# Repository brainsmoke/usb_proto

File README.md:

# USB-C powered boards with programmable USB connectivity

This repository contains a few boards aimed at rapid prototyping.

The main idea is to save time by providing often-used components
and a microcontroller that can act as a USB-serial to UART
(usb-cdc-acm) device, a HID keyboard/keypad or run other simple
programs.

# Firmware (seems to work, no guarantees!)

* [usb_serial](firmware/usb_serial) USB serial to UART adapter firmware, with RTS/DTR signals & reset/boot signals for directly programming ESP32s.
* [usb_hid_keymatrix](firmware/usb_hid_keymatrix) USB HID Keypad firmware, for a keyboard matrix (max. 16 keys)
* [usb_hid_keymatrix](firmware/usb_hid_keymatrix_5x5) USB HID Keypad firmware, for a keyboard matrix (max. 25 keys)
* [usb_hid_simple](firmware/usb_hid_simple) USB HID Keypad firmware for a few buttons
* [flappy](firmware/flappy) Flappy bird controller / spacebar only USB HID Keypad
* [game_controller](firmware/game_controller) Gamepad controller / USB HID Keypad
* [popcalc](firmware/popcalc) USB device that 'pops calc'
* [led_segment_tester](firmware/led_segment_tester) tester firmware for a LED installation
* [obegraensad](firmware/obegraensad) USB-serial to 16 bit IKEA OBEGRÄNSAD display driver

# PCBs

## A protoboard with an STM32F042 for usb connectivity & GPIO / UART functionality.

Production files (JLCPCB): [gerbers](build/usb_proto/gerbers_jlc.zip) [BOM](build/usb_proto/bomfile_jlc.csv) [POS](build/usb_proto/posfile_jlc.csv)

Cases: [basic](build/usb_proto/case.stl) [hexagon](build/usb_proto/case_almost_regular_hexagon.stl) [keyswitches](build/usb_proto/case_keyswitches_8.stl) [led strips](build/usb_proto/case_led_strip_connector.stl)

* 5v USB-C fed (with 5k1 resistors for true USB-C compatibility)
* 3v3 linear regulator
* STM32F042G6 microcontroller (with xtal-less 12mbit USB support)
* A button to boot the STM32 in DFU mode
* GPIO Port A pins 0 to 7 broken out
* GPIO Port B pins 6 & 7 broken out (for UART TX/RX)
* 4 general purpose LEDs
* 3 general purpose buttons
* A 21 column breadboard-style protoboard
* size: 47x77mm
* 4 M3 holes 40mm and 70mm apart

## An STM32F042 breakout board

Production files (JLCPCB): [gerbers](build/usb_mini_io/gerbers_jlc.zip) [BOM](build/usb_mini_io/bomfile_jlc.csv) [POS](build/usb_mini_io/posfile_jlc.csv)

Cases: [keypad (keycaps flush)](build/usb_mini_io/keypad.stl) [keypad (keyswitches visible)](build/usb_mini_io/old_keypad.stl) [single key controller](build/usb_mini_io/single_key.stl)

* for smaller enclosures (27x22mm)
* I/O & firmware compatible with the protoboard
* 5v USB-C fed (with 5k1 resistors for true USB-C compatibility)
* 3v3 linear regulator
* STM32F042G6 microcontroller (with xtal-less 12mbit USB support)
* A button to boot the STM32 in DFU mode
* no LEDs / general purpose buttons / protoboard space
* 2 M3 holes 20mm apart

# USB <-> USB 'null-modem' (but electrically isolated) [UNTESTED]

# JTAG/SWD programmer with USB-C connector
 
Production files (JLCPCB): [gerbers](build/swd_prog/gerbers_jlc.zip) [BOM](build/swd_prog/bomfile_jlc.csv) [POS](build/swd_prog/posfile_jlc.csv)
 
Cases: [basic](build/swd_prog/case.stl) [all headers](build/swd_prog/case_add.stl)

# Padauk programmer with USB-C connector

Production files (JLCPCB): [gerbers](build/pdk_prog/gerbers_jlc.zip) [BOM](build/pdk_prog/bomfile_jlc.csv) [POS](build/pdk_prog/posfile_jlc.csv)
 
Case: [case](build/pdk_prog/case.stl)

## (old) USB-C Fed Protoboard

The first version of the protoboard did not have a microcontroller:
[pcb/simple](pcb/simple)

# License

* The hardware (schematic / PCB / production files / case models ) is Licensed CC-BY-4.0
* The firmware (in the firmware directory) uses libopencm3 which is licensed LGPLv3 and
  all code specific to this project is distributed under the MIT license.
* This repo contains nothing vibe-coded
* LLM assisted contributions not welcome

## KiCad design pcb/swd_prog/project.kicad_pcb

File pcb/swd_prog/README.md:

# JTAG/SWD programmer with USB-C connector

Production files (JLCPCB): [gerbers](../../build/swd_prog/gerbers_jlc.zip) [BOM](../../build/swd_prog/bomfile_jlc.csv) [POS](../../build/swd_prog/posfile_jlc.csv)

Cases: [basic](../../build/swd_prog/case.stl), [all headers](../../build/swd_prog/case_all.stl)

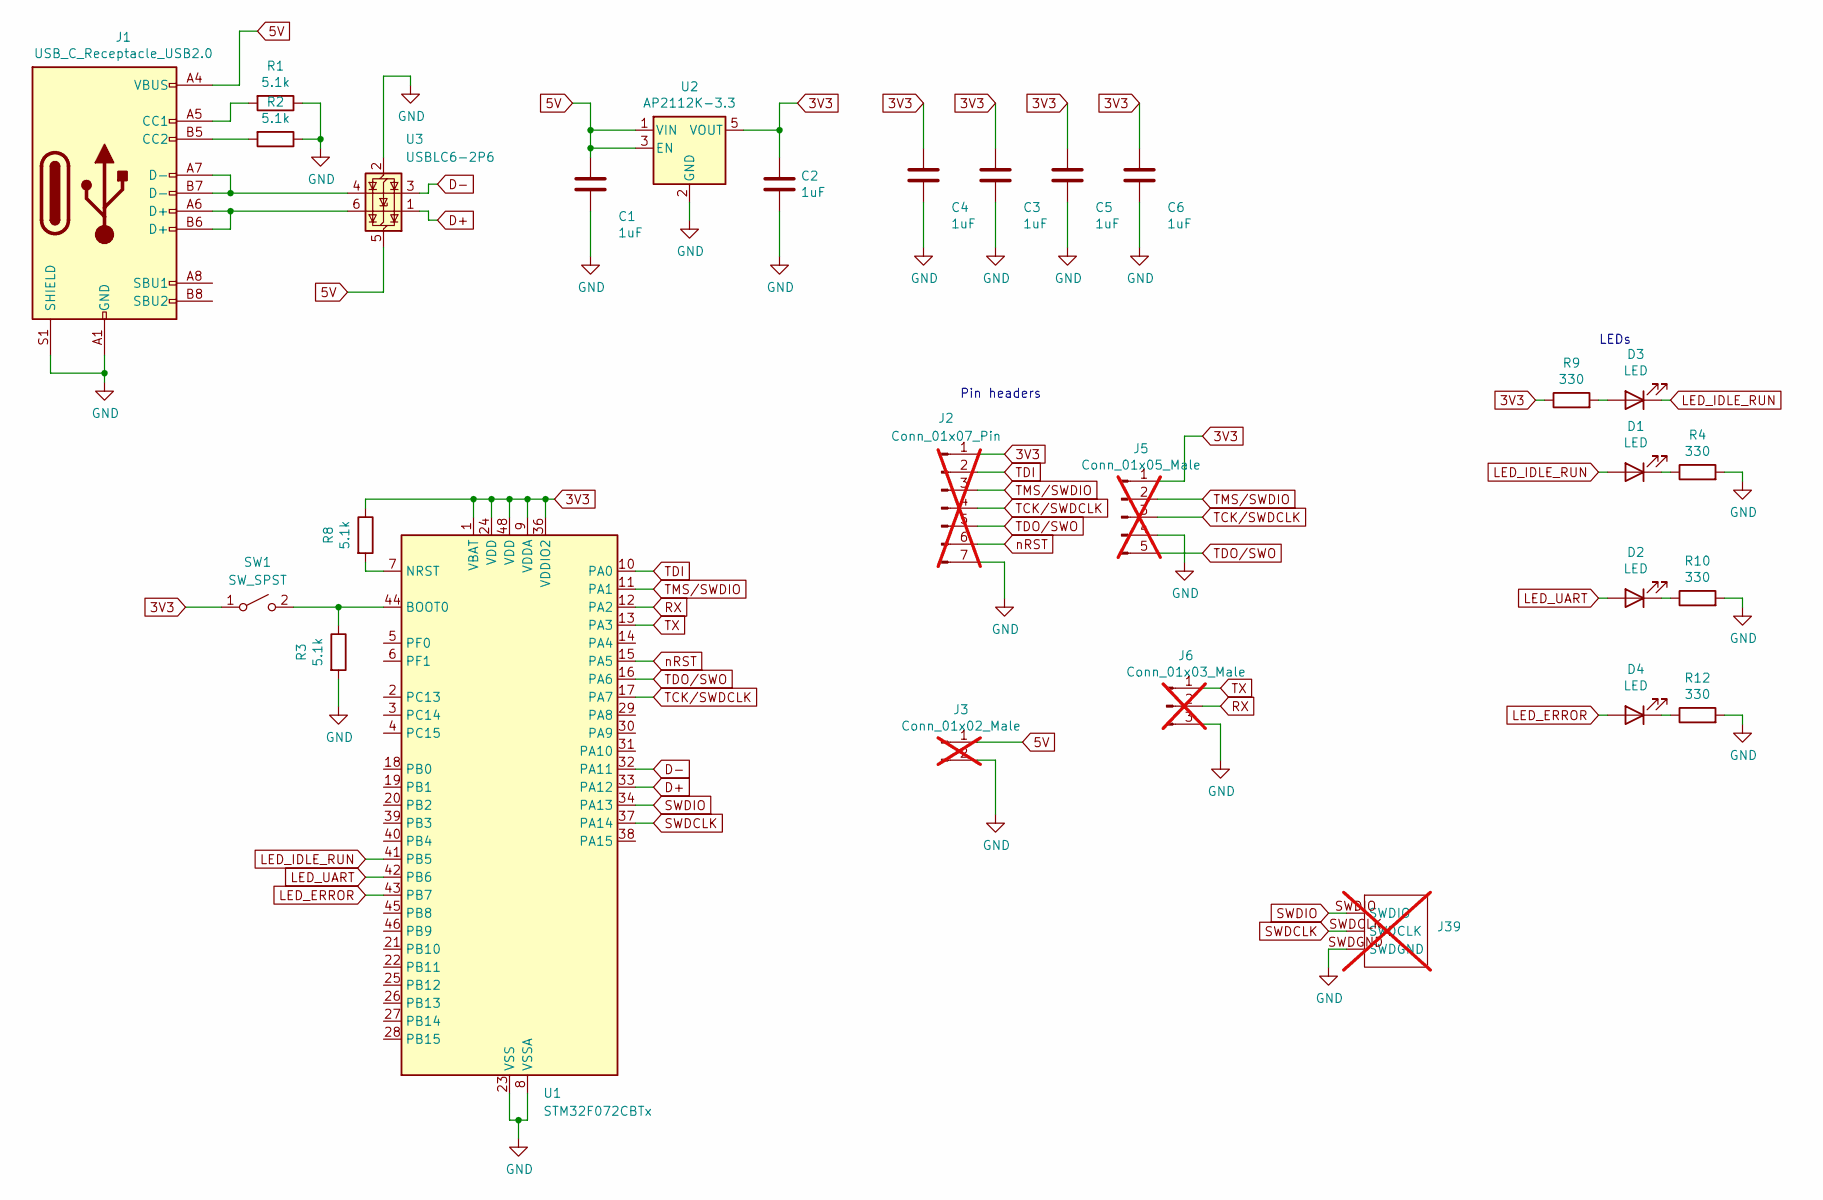
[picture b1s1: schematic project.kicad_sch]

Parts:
C1, C2, C3, C4, C5, C6: 1uF; C_0402_1005Metric; LCSC C52923
D1: LED; LED_0603_1608Metric; LCSC C72038
D2, D3: LED; LED_0603_1608Metric; LCSC C12065
D4: LED; LED_0603_1608Metric; LCSC C2286
J1: USB_C_Receptacle_USB2.0; USB_C_Receptacle_HRO_TYPE-C-31-M-12; LCSC C165948
J2: Conn_01x07_Pin; PinHeader_1x07_P2.54mm_Vertical; not fitted
J3: Conn_01x02_Male; PinHeader_1x02_P2.54mm_Vertical; not fitted
J5: Conn_01x05_Male; PinHeader_1x05_P2.54mm_Vertical; not fitted
J6: Conn_01x03_Male; PinHeader_1x03_P2.54mm_Vertical; not fitted
J39: SWDHeader_covered; not fitted
R1, R2, R3, R8: 5.1k; R_0402_1005Metric; LCSC C25905
R4, R9, R10, R12: 330; R_0402_1005Metric; LCSC C25104
SW1: SW_SPST; SW_Push_1P1T_NO_CK_KMR2; LCSC C318893
U1: STM32F072CBTx; LQFP-48_7x7mm_P0.5mm; LCSC C81720
U2: AP2112K-3.3; SOT-23-5; LCSC C51118
U3: USBLC6-2P6; SOT-666; LCSC C15999

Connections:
3V3: C2.1, C3.1, C4.1, C5.1, C6.1, J2.1, J5.1, R8.1, R9.1, SW1.1 (A), U1.1 (VBAT), U1.9 (VDDA), U1.24 (VDD), U1.36 (VDDIO2), U1.48 (VDD), U2.5 (VOUT)
5V: C1.1, J1.A4 (VBUS), J1.A9 (VBUS), J1.B4 (VBUS), J1.B9 (VBUS), J3.1, U2.1 (VIN), U2.3 (EN), U3.5 (VBUS)
D+: U1.33 (PA12), U3.1 (I/O1)
D-: U1.32 (PA11), U3.3 (I/O2)
GND: C1.2, C2.2, C3.2, C4.2, C5.2, C6.2, J1.A1 (GND), J1.A12 (GND), J1.B1 (GND), J1.B12 (GND), J1.S1 (SHIELD), J2.7, J3.2, J5.4, J6.3, J39.SWDGND, R1.1, R2.1, R3.2, R4.2, R10.2, R12.2, U1.8 (VSSA), U1.23 (VSS), U1.35 (VSS), U1.47 (VSS), U2.2 (GND), U3.2 (GND)
LED_ERROR: D4.2 (A), U1.43 (PB7)
LED_IDLE_RUN: D1.2 (A), D3.1 (K), U1.41 (PB5)
LED_UART: D2.2 (A), U1.42 (PB6)
unnamed: D1.1 (K), R4.1
unnamed: D2.1 (K), R10.1
unnamed: D3.2 (A), R9.2
unnamed: D4.1 (K), R12.1
unnamed: J1.A5 (CC1), R1.2
unnamed: J1.B5 (CC2), R2.2
unnamed: J1.A6 (D+), J1.B6 (D+), U3.6 (I/O1)
unnamed: J1.A7 (D-), J1.B7 (D-), U3.4 (I/O2)
unnamed: R3.1, SW1.2 (B), U1.44 (BOOT0)
unnamed: R8.2, U1.7 (NRST)
RX: J6.2, U1.12 (PA2)
SWDCLK: J39.SWDCLK, U1.37 (PA14)
SWDIO: J39.SWDIO, U1.34 (PA13)
TCK/SWDCLK: J2.4, J5.3, U1.17 (PA7)
TDI: J2.2, U1.10 (PA0)
TDO/SWO: J2.5, J5.5, U1.16 (PA6)
TMS/SWDIO: J2.3, J5.2, U1.11 (PA1)
TX: J6.1, U1.13 (PA3)
nRST: J2.6, U1.15 (PA5)

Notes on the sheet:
Pin headers
LEDs

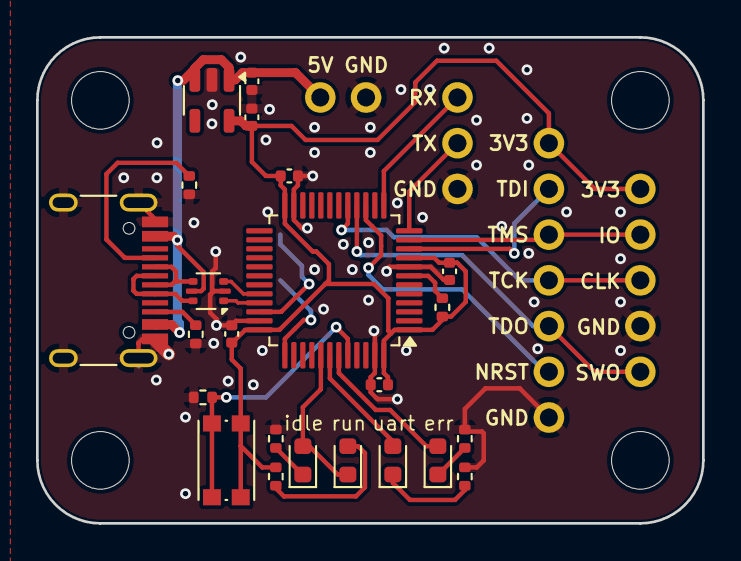
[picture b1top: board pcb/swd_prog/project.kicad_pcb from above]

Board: 2 copper layers, 37.0 x 27.0 mm, 28 parts (1 on the bottom side), 27 nets.

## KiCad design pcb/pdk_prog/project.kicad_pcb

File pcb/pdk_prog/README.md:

# Padauk programmer with USB-C connector

Production files (JLCPCB): [gerbers](../../build/pdk_prog/gerbers_jlc.zip) [BOM](../../build/pdk_prog/bomfile_jlc.csv) [POS](../../build/pdk_prog/posfile_jlc.csv)

Case: [case](../../build/pdk_prog/case.stl)

Circuit adapted from:

  https://github.com/free-pdk/easy-pdk-programmer-lite-hardware

Which in turn was adapted from:

  https://github.com/free-pdk/easy-pdk-programmer-hardware

Runs:

  https://github.com/free-pdk/easy-pdk-programmer-software

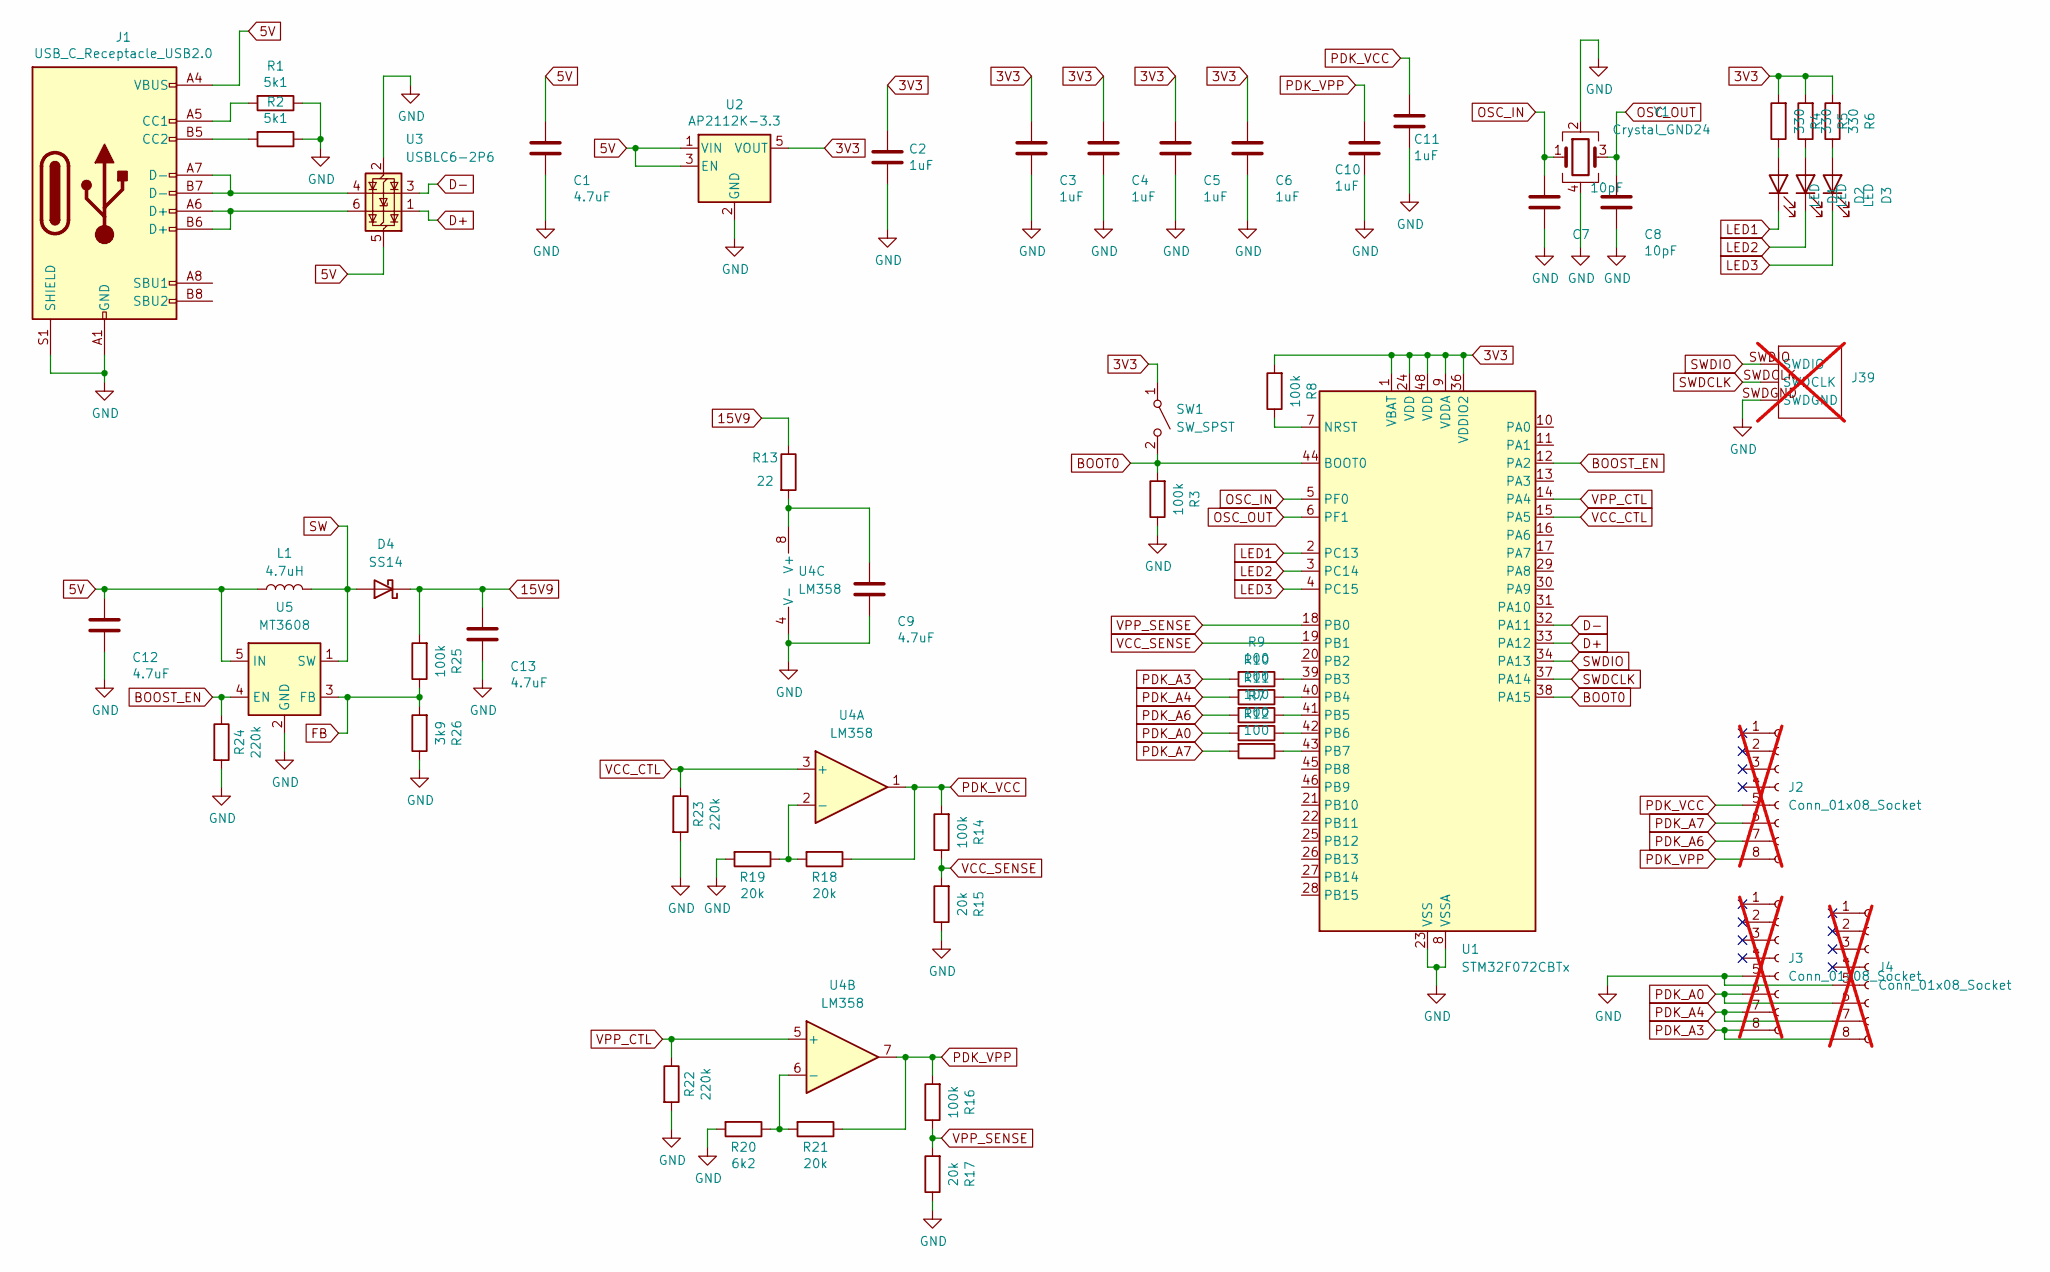
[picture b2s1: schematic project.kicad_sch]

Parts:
C1, C9, C12, C13: 4.7uF; C_0603_1608Metric; LCSC C19666
C2, C3, C4, C5, C6, C10, C11: 1uF; C_0402_1005Metric; LCSC C52923
C7, C8: 10pF; C_0402_1005Metric; LCSC C32949
D1, D2, D3: LED; LED_0603_1608Metric; LCSC C2286
D4: SS14; D_SMA; LCSC C2480
J1: USB_C_Receptacle_USB2.0; USB_C_Receptacle_HRO_TYPE-C-31-M-12; LCSC C165948
J2, J3, J4: Conn_01x08_Socket; PinSocket_1x08_P2.54mm_Vertical; not fitted
J39: SWDHeader_covered; not fitted
L1: 4.7uH; L_Wuerth_MAPI-3015; LCSC C7427089
R1, R2: 5k1; R_0402_1005Metric; LCSC C25905
R3, R8, R14, R16, R25: 100k; R_0402_1005Metric; LCSC C25741
R4, R5, R6: 330; R_0402_1005Metric; LCSC C25104
R7, R9, R10, R11, R12: 100; R_0402_1005Metric; LCSC C25076
R13: 22; R_0402_1005Metric; LCSC C25092
R15, R17, R18, R19, R21: 20k; R_0402_1005Metric; LCSC C25765
R20: 6k2; R_0603_1608Metric; LCSC C4260
R22, R23, R24: 220k; R_0402_1005Metric; LCSC C25767
R26: 3k9; R_0402_1005Metric; LCSC C51721
SW1: SW_SPST; SW_Push_1P1T_NO_CK_KMR2; LCSC C318893
U1: STM32F072CBTx; LQFP-48_7x7mm_P0.5mm; LCSC C81720
U2: AP2112K-3.3; SOT-23-5; LCSC C51118
U3: USBLC6-2P6; SOT-666; LCSC C15999
U4: LM358; SOIC-8_3.9x4.9mm_P1.27mm; LCSC C7950
U5: MT3608; SOT-23-6; LCSC C84817
Y1: Crystal_GND24; Crystal_SMD_3225-4Pin_3.2x2.5mm; LCSC C400090

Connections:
3V3: C2.1, C3.1, C4.1, C5.1, C6.1, R4.2, R5.2, R6.2, R8.2, SW1.1 (A), U1.1 (VBAT), U1.9 (VDDA), U1.24 (VDD), U1.36 (VDDIO2), U1.48 (VDD), U2.5 (VOUT)
5V: C1.1, C12.1, J1.A4 (VBUS), J1.A9 (VBUS), J1.B4 (VBUS), J1.B9 (VBUS), L1.1, U2.1 (VIN), U2.3 (EN), U3.5 (VBUS), U5.5 (IN)
15V9: C13.1, D4.1 (K), R13.1, R25.2
BOOST_EN: R24.1, U1.12 (PA2), U5.4 (EN)
BOOT0: R3.2, SW1.2 (B), U1.38 (PA15), U1.44 (BOOT0)
D+: U1.33 (PA12), U3.1 (I/O1)
D-: U1.32 (PA11), U3.3 (I/O2)
FB: R25.1, R26.2, U5.3 (FB)
GND: C1.2, C2.2, C3.2, C4.2, C5.2, C6.2, C7.2, C8.2, C9.2, C10.2, C11.2, C12.2, C13.2, J1.A1 (GND), J1.A12 (GND), J1.B1 (GND), J1.B12 (GND), J1.S1 (SHIELD), J3.5, J4.5, J39.SWDGND, R1.1, R2.1, R3.1, R15.1, R17.1, R19.2, R20.2, R22.2, R23.2, R24.2, R26.1, U1.8 (VSSA), U1.23 (VSS), U1.35 (VSS), U1.47 (VSS), U2.2 (GND), U3.2 (GND), U4.4 (V-), U5.2 (GND), Y1.2, Y1.4
LED1: D1.1 (K), U1.2 (PC13)
LED2: D2.1 (K), U1.3 (PC14)
LED3: D3.1 (K), U1.4 (PC15)
unnamed: D1.2 (A), R4.1
unnamed: D2.2 (A), R5.1
unnamed: D3.2 (A), R6.1
unnamed: J1.A5 (CC1), R1.2
unnamed: J1.B5 (CC2), R2.2
unnamed: J1.A6 (D+), J1.B6 (D+), U3.6 (I/O1)
unnamed: J1.A7 (D-), J1.B7 (D-), U3.4 (I/O2)
unnamed: R8.1, U1.7 (NRST)
unnamed: R9.1, U1.39 (PB3)
unnamed: R10.1, U1.40 (PB4)
unnamed: R11.1, U1.41 (PB5)
unnamed: R7.1, U1.42 (PB6)
unnamed: R12.1, U1.43 (PB7)
unnamed: R18.2, R19.1, U4.2 (-)
unnamed: R20.1, R21.2, U4.6 (-)
unnamed: C9.1, R13.2, U4.8 (V+)
OSC_IN: C7.1, U1.5 (PF0), Y1.1
OSC_OUT: C8.1, U1.6 (PF1), Y1.3
PDK_A0: J3.6, J4.6, R7.2
PDK_A3: J3.8, J4.8, R9.2
PDK_A4: J3.7, J4.7, R10.2
PDK_A6: J2.7, R11.2
PDK_A7: J2.6, R12.2
PDK_VCC: C11.1, J2.5, R14.2, R18.1, U4.1
PDK_VPP: C10.1, J2.8, R16.2, R21.1, U4.7
SW: D4.2 (A), L1.2, U5.1 (SW)
SWDCLK: J39.SWDCLK, U1.37 (PA14)
SWDIO: J39.SWDIO, U1.34 (PA13)
VCC_CTL: R23.1, U1.15 (PA5), U4.3 (+)
VCC_SENSE: R14.1, R15.2, U1.19 (PB1)
VPP_CTL: R22.1, U1.14 (PA4), U4.5 (+)
VPP_SENSE: R16.1, R17.2, U1.18 (PB0)

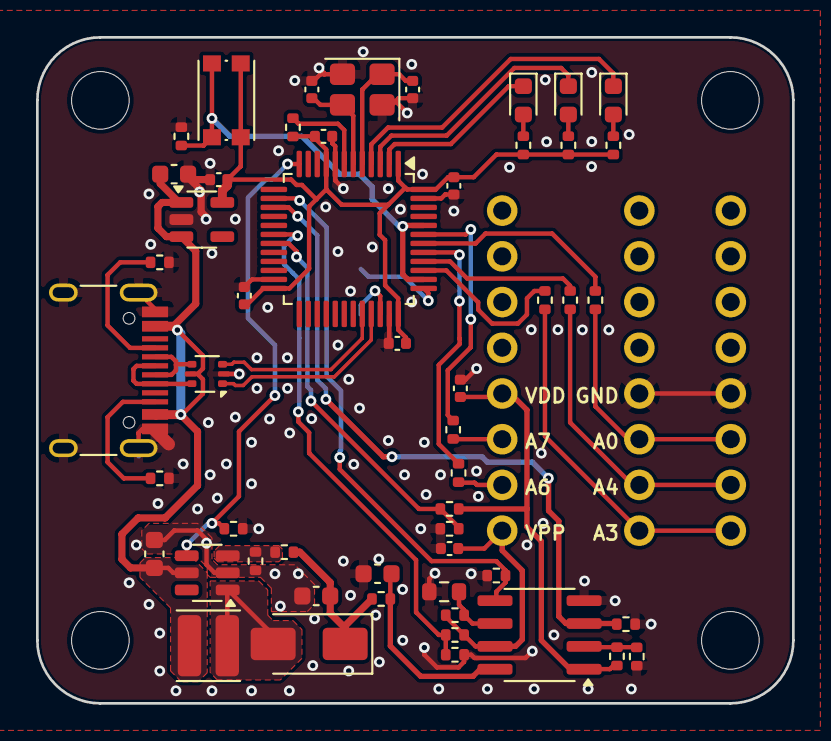
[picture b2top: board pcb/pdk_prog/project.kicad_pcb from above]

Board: 2 copper layers, 42.0 x 37.0 mm, 56 parts (1 on the bottom side), 44 nets.

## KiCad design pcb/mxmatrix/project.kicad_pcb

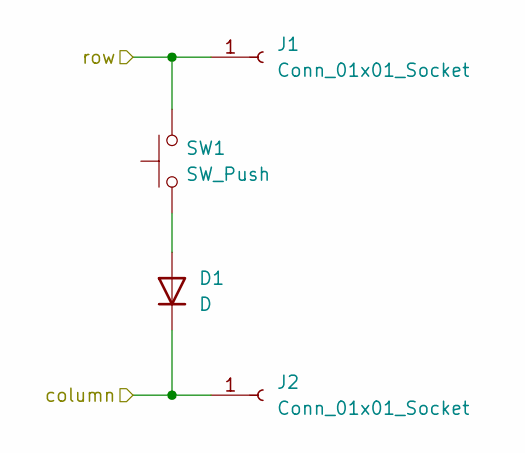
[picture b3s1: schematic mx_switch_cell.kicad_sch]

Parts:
D1: D; D_SOD-123
J1, J2: Conn_01x01_Socket; PinSocket_1x01_P2.54mm_Vertical
SW1: SW_Push; SW_Cherry_MX_1.00u_PCB

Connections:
/mx_switch_cell/column: D1.1 (K), J2.1; also elsewhere on the board
/mx_switch_cell/row: J1.1, SW1.2; also elsewhere on the board
unnamed: D1.2 (A), SW1.1

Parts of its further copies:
D2, D3, D4, D5, D6, D7, D8, D9, D10, D11, D12, D13, D14, D15, D16, D17, D18, D19, D20, D21, D22, D23, D24, D25: D; D_SOD-123
J3, J4, J5, J6, J7, J8, J9, J10, J11, J12, J13, J14, J15, J16, J17, J18, J19, J20, J21, J22, J23, J24, J25, J26, J27, J28, J29, J30, J31, J32, J33, J34, J35, J36, J37, J38, J39, J40, J41, J42, J43, J44, J45, J46, J47, J48, J49, J50: Conn_01x01_Socket; PinSocket_1x01_P2.54mm_Vertical
SW2, SW3, SW4, SW5, SW6, SW7, SW8, SW9, SW10, SW11, SW12, SW13, SW14, SW15, SW16, SW17, SW18, SW19, SW20, SW21, SW22, SW23, SW24, SW25: SW_Push; SW_Cherry_MX_1.00u_PCB

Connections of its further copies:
/mx_switch_cell1/row: J3.1, J13.1, J23.1, J33.1, J43.1, SW2.2, SW7.2, SW12.2, SW17.2, SW22.2
/mx_switch_cell5/column: D6.1 (K), D7.1 (K), D8.1 (K), D9.1 (K), D10.1 (K), J12.1, J14.1, J16.1, J18.1, J20.1
/mx_switch_cell10/column: D11.1 (K), D12.1 (K), D13.1 (K), D14.1 (K), D15.1 (K), J22.1, J24.1, J26.1, J28.1, J30.1
/mx_switch_cell12/row: J5.1, J15.1, J25.1, J35.1, J45.1, SW3.2, SW8.2, SW13.2, SW18.2, SW23.2
/mx_switch_cell13/row: J7.1, J17.1, J27.1, J37.1, J47.1, SW4.2, SW9.2, SW14.2, SW19.2, SW24.2
/mx_switch_cell14/row: J9.1, J19.1, J29.1, J39.1, J49.1, SW5.2, SW10.2, SW15.2, SW20.2, SW25.2
/mx_switch_cell15/column: D16.1 (K), D17.1 (K), D18.1 (K), D19.1 (K), D20.1 (K), J32.1, J34.1, J36.1, J38.1, J40.1
/mx_switch_cell20/column: D21.1 (K), D22.1 (K), D23.1 (K), D24.1 (K), D25.1 (K), J42.1, J44.1, J46.1, J48.1, J50.1
/mx_switch_cell/column: D2.1 (K), D3.1 (K), D4.1 (K), D5.1 (K), J4.1, J6.1, J8.1, J10.1; also elsewhere on the board
/mx_switch_cell/row: J11.1, J21.1, J31.1, J41.1, SW6.2, SW11.2, SW16.2, SW21.2; also elsewhere on the board
unnamed: D2.2 (A), SW2.1
unnamed: D3.2 (A), SW3.1
unnamed: D4.2 (A), SW4.1
unnamed: D5.2 (A), SW5.1
unnamed: D6.2 (A), SW6.1
unnamed: D7.2 (A), SW7.1
unnamed: D8.2 (A), SW8.1
unnamed: D9.2 (A), SW9.1
unnamed: D10.2 (A), SW10.1
unnamed: D11.2 (A), SW11.1
unnamed: D12.2 (A), SW12.1
unnamed: D13.2 (A), SW13.1
unnamed: D14.2 (A), SW14.1
unnamed: D15.2 (A), SW15.1
unnamed: D16.2 (A), SW16.1
unnamed: D17.2 (A), SW17.1
unnamed: D18.2 (A), SW18.1
unnamed: D19.2 (A), SW19.1
unnamed: D20.2 (A), SW20.1
unnamed: D21.2 (A), SW21.1
unnamed: D22.2 (A), SW22.1
unnamed: D23.2 (A), SW23.1
unnamed: D24.2 (A), SW24.1
unnamed: D25.2 (A), SW25.1

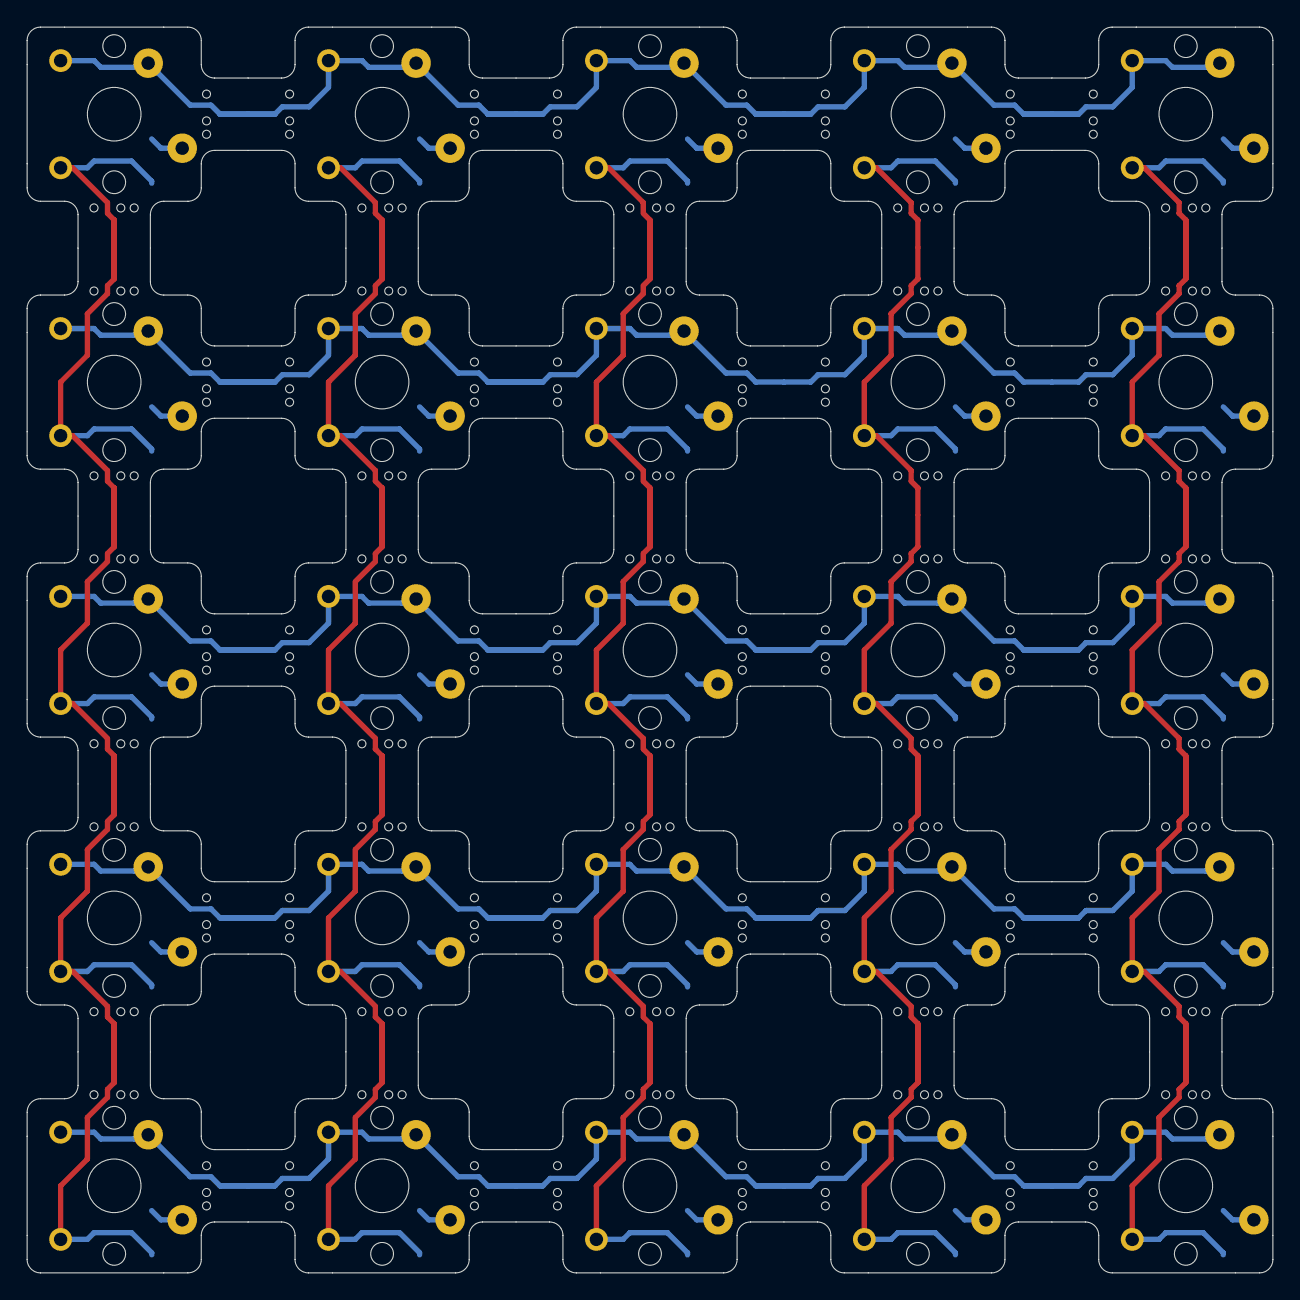
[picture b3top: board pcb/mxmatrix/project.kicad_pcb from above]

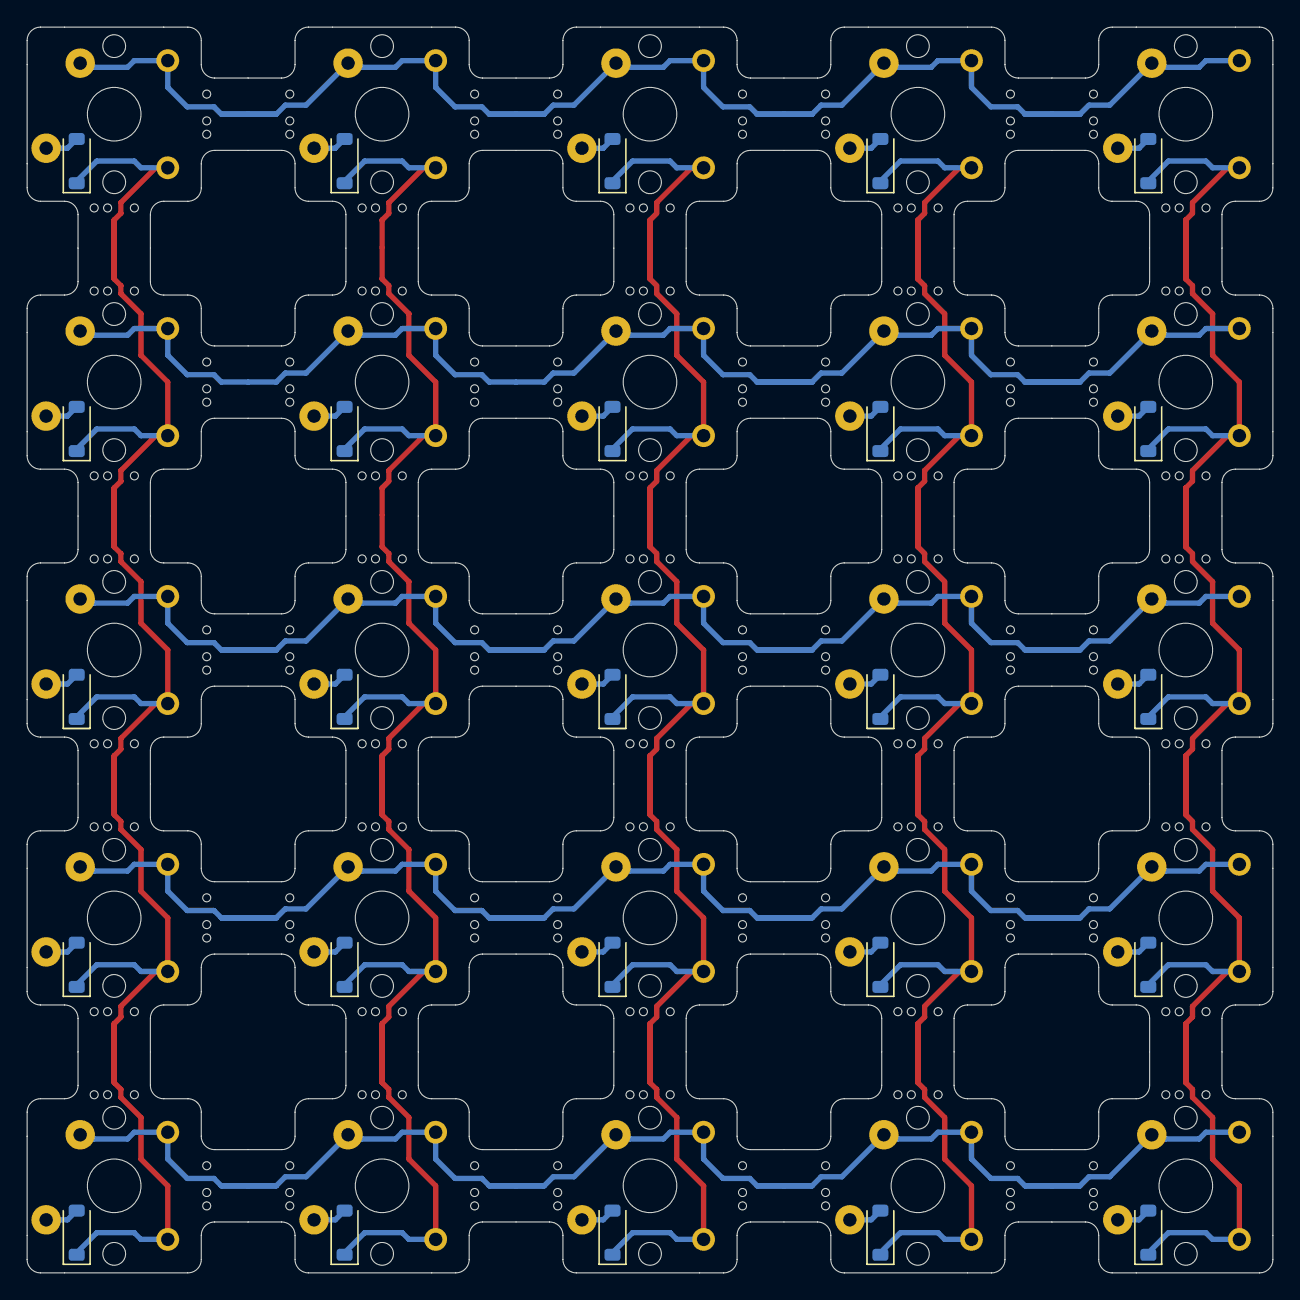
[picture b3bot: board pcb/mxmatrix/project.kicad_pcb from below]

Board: 2 copper layers, 93.0 x 93.0 mm, 100 parts (75 on the bottom side), 35 nets.

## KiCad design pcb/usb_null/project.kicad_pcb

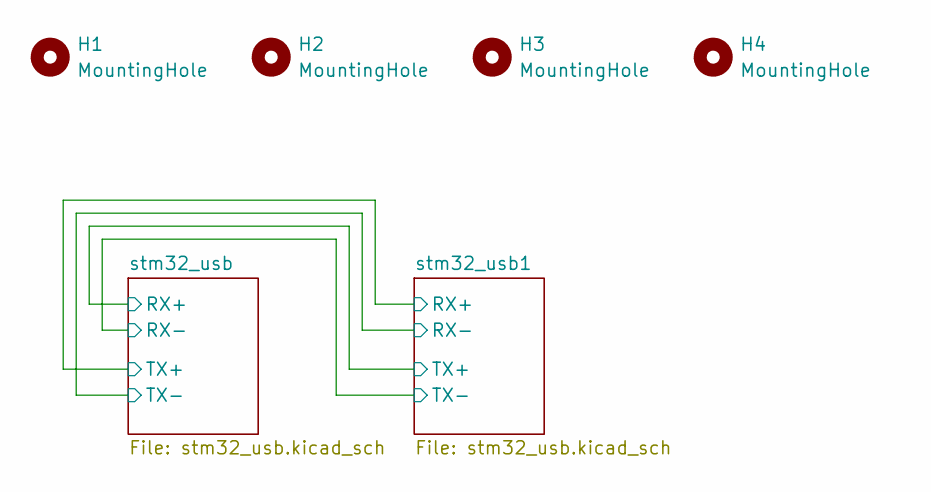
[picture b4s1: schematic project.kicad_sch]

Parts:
H1, H2, H3, H4: MountingHole; MountingHole_3.2mm_M3_DIN965

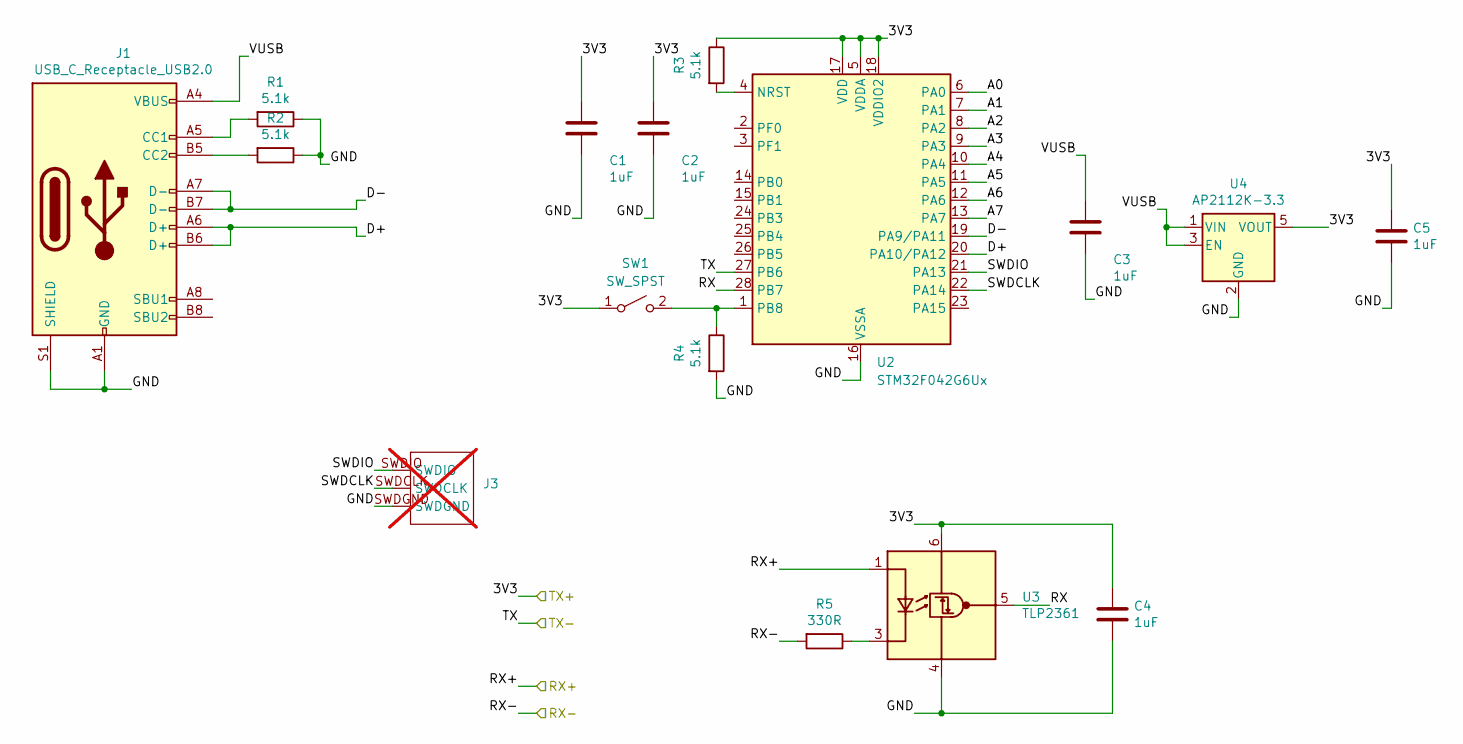
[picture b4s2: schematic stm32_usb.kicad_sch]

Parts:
C1, C2, C3, C4, C5: 1uF; C_0402_1005Metric; LCSC C52923
J1: USB_C_Receptacle_USB2.0; USB_C_Receptacle_HRO_TYPE-C-31-M-12; LCSC C165948
J3: SWDHeader; not fitted
R1, R2, R3, R4: 5.1k; R_0402_1005Metric; LCSC C25905
R5: 330R; R_0402_1005Metric; LCSC C25104
SW1: SW_SPST; SW_Push_1P1T_NO_CK_KMR2; LCSC C318893
U2: STM32F042G6Ux; QFN-28_4x4mm_P0.5mm; LCSC C961597
U3: TLP2361; SO-5_4.4x3.6mm_P1.27mm; LCSC C107626
U4: AP2112K-3.3; SOT-23-5; LCSC C51118

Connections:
/stm32_usb/3V3: C1.1, C2.1, C4.1, C5.1, R3.1, SW1.1 (A), U2.5 (VDDA), U2.17 (VDD), U2.18 (VDDIO2), U3.6 (VDD), U4.5 (VOUT); also elsewhere on the board
/stm32_usb/A0: U2.6 (PA0)
/stm32_usb/A1: U2.7 (PA1)
/stm32_usb/A2: U2.8 (PA2)
/stm32_usb/A3: U2.9 (PA3)
/stm32_usb/A4: U2.10 (PA4)
/stm32_usb/A5: U2.11 (PA5)
/stm32_usb/A6: U2.12 (PA6)
/stm32_usb/A7: U2.13 (PA7)
/stm32_usb/D+: J1.A6 (D+), J1.B6 (D+), U2.20 (PA10/PA12)
/stm32_usb/D-: J1.A7 (D-), J1.B7 (D-), U2.19 (PA9/PA11)
/stm32_usb/GND: C1.2, C2.2, C3.2, C4.2, C5.2, J1.A1 (GND), J1.A12 (GND), J1.B1 (GND), J1.B12 (GND), J1.S1 (SHIELD), J3.SWDGND, R1.1, R2.1, R4.2, U2.16 (VSSA), U3.4 (GND), U4.2 (GND)
/stm32_usb/RX: U2.28 (PB7), U3.5 (VO)
/stm32_usb/RX+: U3.1 (A); also elsewhere on the board
/stm32_usb/RX-: R5.2; also elsewhere on the board
/stm32_usb/SWDCLK: J3.SWDCLK, U2.22 (PA14)
/stm32_usb/SWDIO: J3.SWDIO, U2.21 (PA13)
/stm32_usb/TX: U2.27 (PB6); also elsewhere on the board
/stm32_usb/VUSB: C3.1, J1.A4 (VBUS), J1.A9 (VBUS), J1.B4 (VBUS), J1.B9 (VBUS), U4.1 (VIN), U4.3 (EN)
unnamed: J1.A5 (CC1), R1.2
unnamed: J1.B5 (CC2), R2.2
unnamed: R4.1, SW1.2 (B), U2.1 (PB8)
unnamed: R3.2, U2.4 (NRST)
unnamed: R5.1, U3.3 (K)

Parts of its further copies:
C6, C7, C8, C9, C10: 1uF; C_0402_1005Metric; LCSC C52923
J4: USB_C_Receptacle_USB2.0; USB_C_Receptacle_HRO_TYPE-C-31-M-12; LCSC C165948
J6: SWDHeader; not fitted
R6, R7, R8, R9: 5.1k; R_0402_1005Metric; LCSC C25905
R10: 330R; R_0402_1005Metric; LCSC C25104
SW2: SW_SPST; SW_Push_1P1T_NO_CK_KMR2; LCSC C318893
U6: STM32F042G6Ux; QFN-28_4x4mm_P0.5mm; LCSC C961597
U7: TLP2361; SO-5_4.4x3.6mm_P1.27mm; LCSC C107626
U8: AP2112K-3.3; SOT-23-5; LCSC C51118

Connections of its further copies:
/stm32_usb1/A0: U6.6 (PA0)
/stm32_usb1/A1: U6.7 (PA1)
/stm32_usb1/A2: U6.8 (PA2)
/stm32_usb1/A3: U6.9 (PA3)
/stm32_usb1/A4: U6.10 (PA4)
/stm32_usb1/A5: U6.11 (PA5)
/stm32_usb1/A6: U6.12 (PA6)
/stm32_usb1/A7: U6.13 (PA7)
/stm32_usb1/D+: J4.A6 (D+), J4.B6 (D+), U6.20 (PA10/PA12)
/stm32_usb1/D-: J4.A7 (D-), J4.B7 (D-), U6.19 (PA9/PA11)
/stm32_usb1/GND: C6.2, C7.2, C8.2, C9.2, C10.2, J4.A1 (GND), J4.A12 (GND), J4.B1 (GND), J4.B12 (GND), J4.S1 (SHIELD), J6.SWDGND, R6.1, R7.1, R9.2, U6.16 (VSSA), U7.4 (GND), U8.2 (GND)
/stm32_usb1/RX: U6.28 (PB7), U7.5 (VO)
/stm32_usb1/SWDCLK: J6.SWDCLK, U6.22 (PA14)
/stm32_usb1/SWDIO: J6.SWDIO, U6.21 (PA13)
/stm32_usb1/VUSB: C8.1, J4.A4 (VBUS), J4.A9 (VBUS), J4.B4 (VBUS), J4.B9 (VBUS), U8.1 (VIN), U8.3 (EN)
/stm32_usb/3V3: U7.1 (A); also elsewhere on the board
/stm32_usb/RX+: C6.1, C7.1, C9.1, C10.1, R8.1, SW2.1 (A), U6.5 (VDDA), U6.17 (VDD), U6.18 (VDDIO2), U7.6 (VDD), U8.5 (VOUT); also elsewhere on the board
/stm32_usb/RX-: U6.27 (PB6); also elsewhere on the board
/stm32_usb/TX: R10.2; also elsewhere on the board
unnamed: J4.A5 (CC1), R6.2
unnamed: J4.B5 (CC2), R7.2
unnamed: R9.1, SW2.2 (B), U6.1 (PB8)
unnamed: R8.2, U6.4 (NRST)
unnamed: R10.1, U7.3 (K)

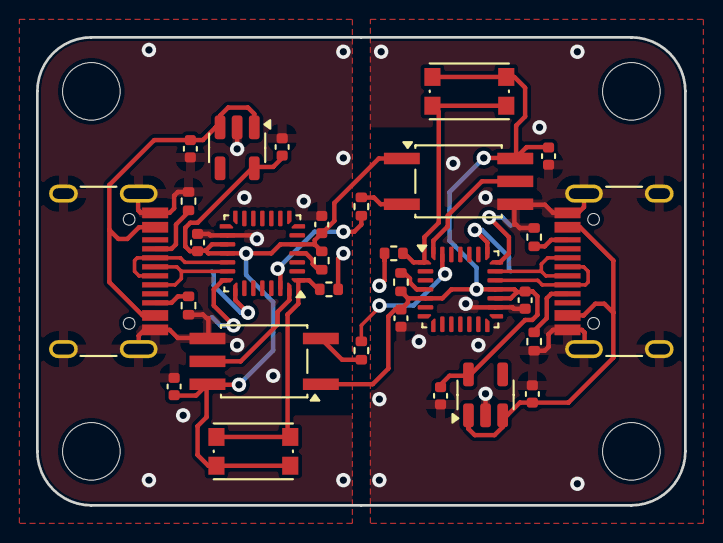
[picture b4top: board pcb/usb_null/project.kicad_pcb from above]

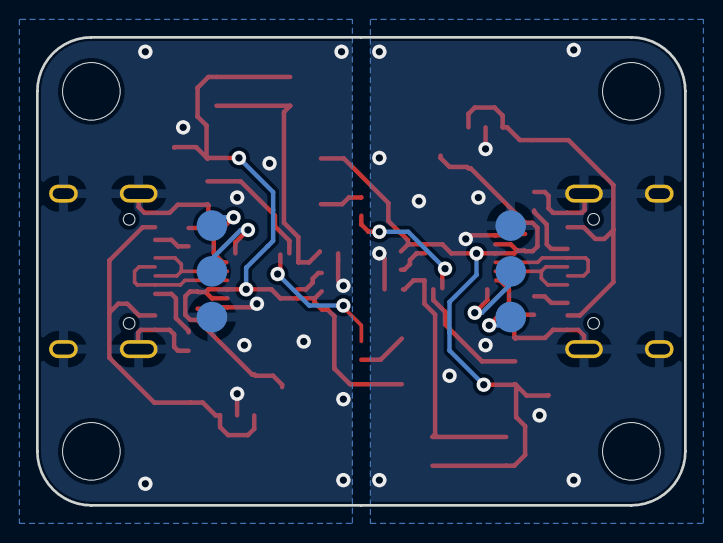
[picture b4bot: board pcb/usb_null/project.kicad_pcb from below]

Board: 2 copper layers, 36.0 x 26.0 mm, 36 parts (2 on the bottom side), 28 nets.

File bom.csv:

"Comment","Designator","Footprint","JLCPCB part #"
"1uF","C1,C2","Capacitor_SMD:C_0603_1608Metric_Pad1.08x0.95mm_HandSolder","C15849"
"USB_C_Receptacle_USB2.0","J1","Connector_USB:USB_C_Receptacle_HRO_TYPE-C-31-M-12","C165948"
"5k1","R1,R2,R3","Resistor_SMD:R_0603_1608Metric_Pad0.98x0.95mm_HandSolder","C23186"
"56k","R4","Resistor_SMD:R_0603_1608Metric_Pad0.98x0.95mm_HandSolder","C23206"
"SW_SPST","SW1,SW2,SW3","Button_Switch_SMD:SW_Push_1P1T_NO_CK_KMR2","C318893"
"AP2112K-3.3","U2","Package_TO_SOT_SMD:SOT-23-5","C51118"
